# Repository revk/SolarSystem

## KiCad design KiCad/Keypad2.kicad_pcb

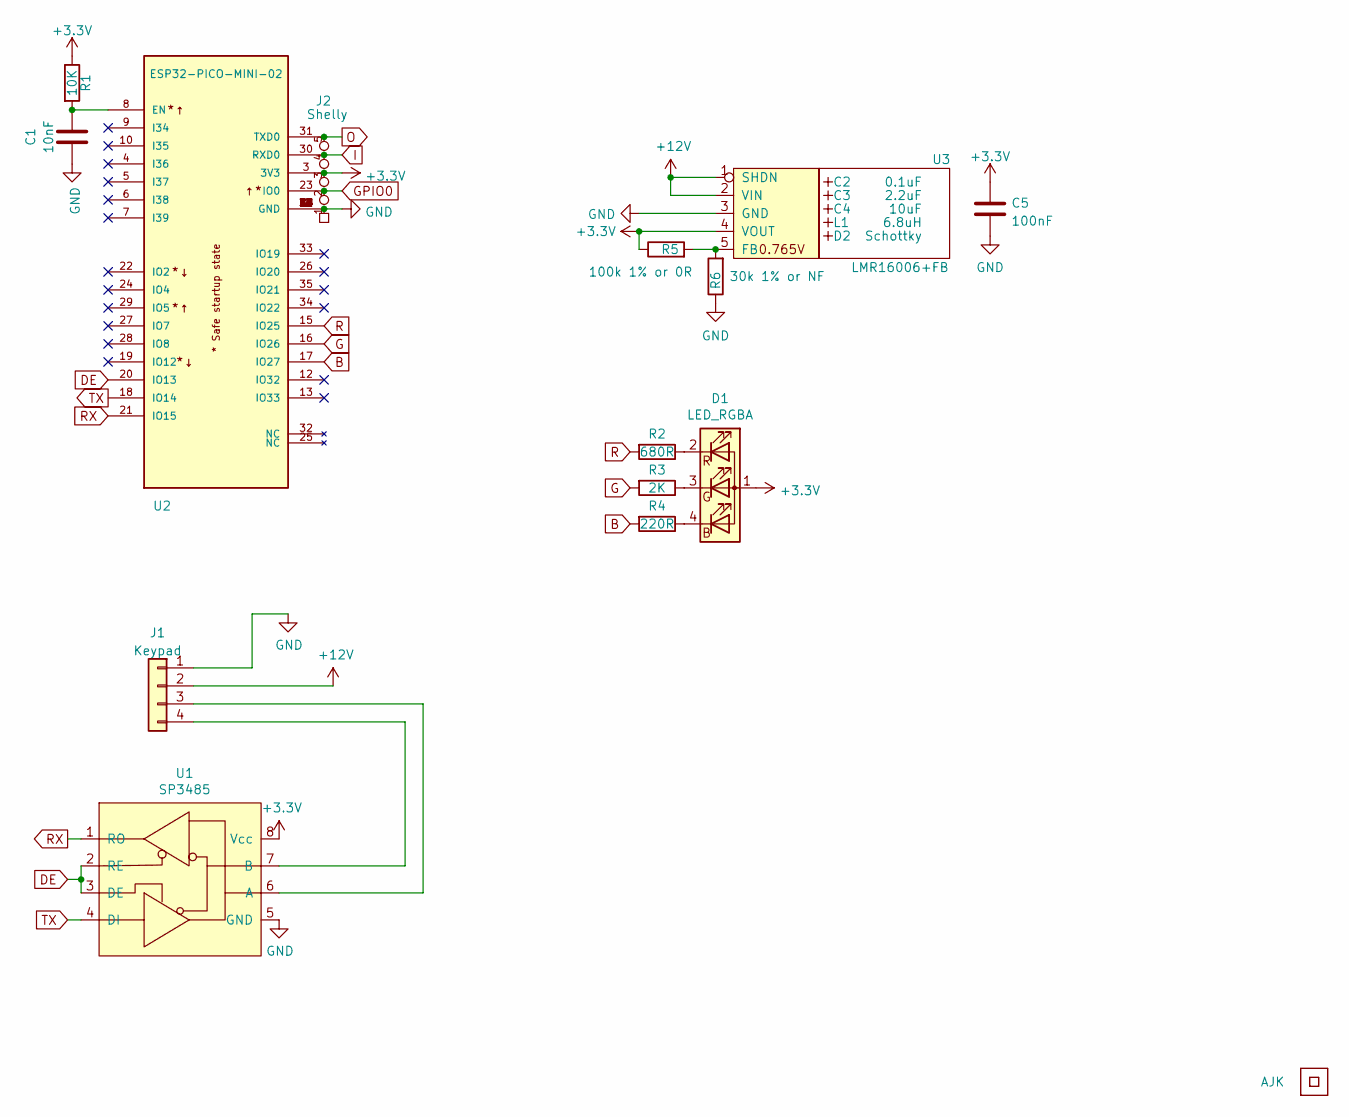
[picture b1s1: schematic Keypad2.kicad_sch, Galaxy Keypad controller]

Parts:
C1: 10nF; C_0603
C2: 0.1uF; C_0603_
C3: 2.2uF; C_0805_
C4: 10uF; C_0805_
C5: 100nF; C_0603
D1: LED_RGBA; LED-RGB-1.6x1.6
D2: Schottky; D_1206_; Part No CD1206-B2100
J1: Keypad; Molex_MiniSPOX_H4V
J2: Shelly
L1: 6.8uH; L_4x4_; Part No TYA4020
Logo1: AJK
R1: 10K; R_0603
R2: 680R; R_0603
R3: 2K; R_0603
R4: 220R; R_0603
R5: 100k 1% or 0R; R_0603
R6: 30k 1% or NF; R_0603
U1: SP3485; SO-8_3.9x4.9mm_P1.27mm
U2: ESP32-PICO-MINI-02; PARTREV v1.0
U3: LMR16006+FB; SOT-23-Thin-6-Reg; Part No LMR16006YQ3
U4: QR; QR-SS

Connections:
+3V3: C5.1, D1.1 (A), J2.3 (3V3), R1.1, R5.1, U1.8 (Vcc), U2.3 (3V3), U3.4 (VOUT)
+12V: J1.2, U3.1 (SHDN), U3.2 (VIN)
B: R4.2, U2.17 (IO27)
DE: U1.2 (RE), U1.3 (DE), U2.20 (IO13)
G: R3.2, U2.16 (IO26)
GND: C1.1, C5.2, J1.1, J2.1 (GND), R6.1, U1.5 (GND), U2.1 (GND), U2.2 (GND), U2.11 (GND), U2.14 (GND), U2.36 (GND), U2.37 (GND), U2.38 (GND), U2.39 (GND), U2.40 (GND), U2.41 (GND), U2.42 (GND), U2.43 (GND), U2.44 (GND), U2.45 (GND), U2.46 (GND), U2.47 (GND), U2.48 (GND), U2.49 (GND), U2.50 (GND), U2.51 (GND), U2.52 (GND), U2.53 (GND), U3.3 (GND)
GPIO0: J2.2 (0), U2.23 (IO0)
I: J2.4 (Rx), U2.30 (RXD0)
unnamed: C1.2, R1.2, U2.8 (EN)
unnamed: D1.2 (RK), R2.1
unnamed: D1.3 (GK), R3.1
unnamed: D1.4 (BK), R4.1
unnamed: J1.3, U1.6 (A)
unnamed: J1.4, U1.7 (B)
unnamed: R5.2, R6.2, U3.5 (FB)
O: J2.5 (Tx), U2.31 (TXD0)
R: R2.2, U2.15 (IO25)
RX: U1.1 (RO), U2.21 (IO15)
TX: U1.4 (DI), U2.18 (IO14)

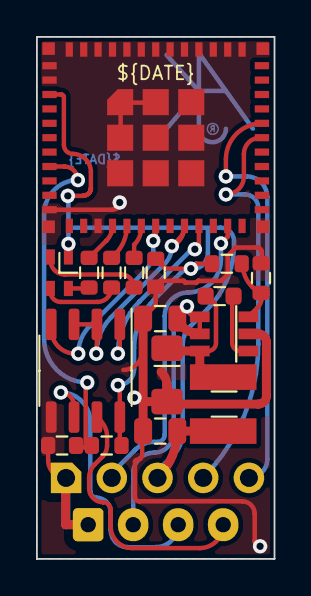
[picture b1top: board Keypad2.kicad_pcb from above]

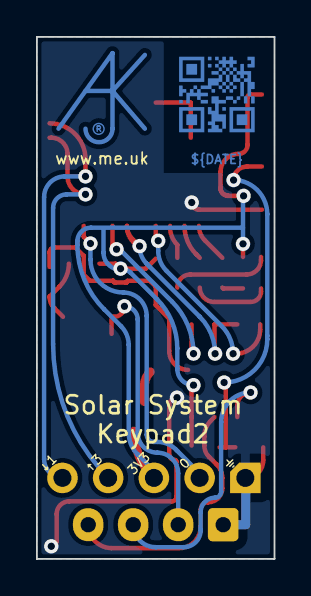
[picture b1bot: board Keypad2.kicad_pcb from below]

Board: 2 copper layers, 13.2 x 29.0 mm, 21 parts (3 on the bottom side), 19 nets.

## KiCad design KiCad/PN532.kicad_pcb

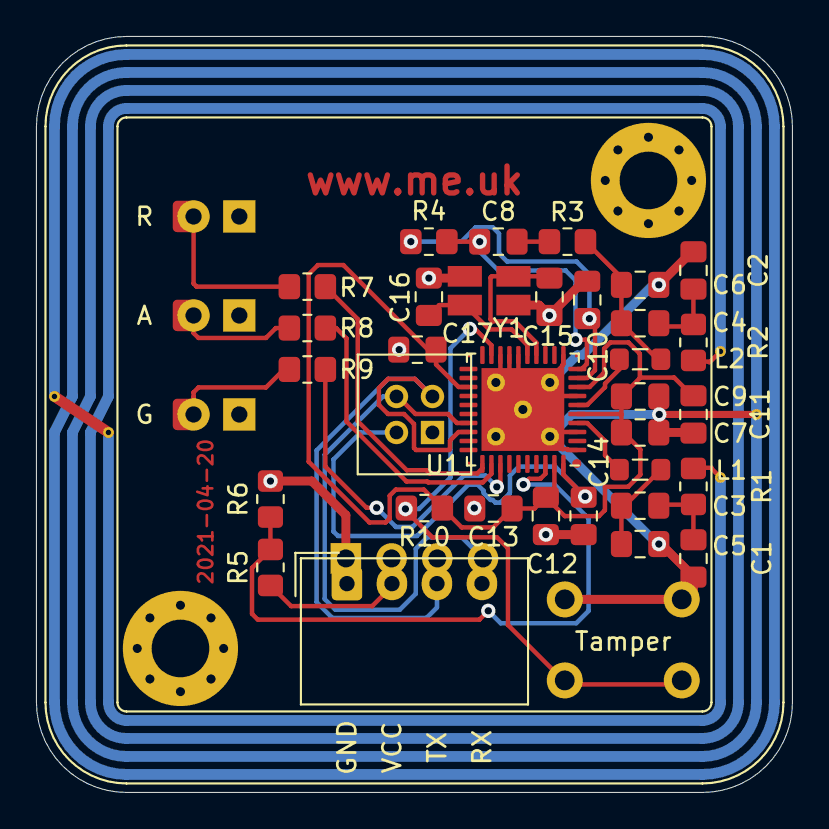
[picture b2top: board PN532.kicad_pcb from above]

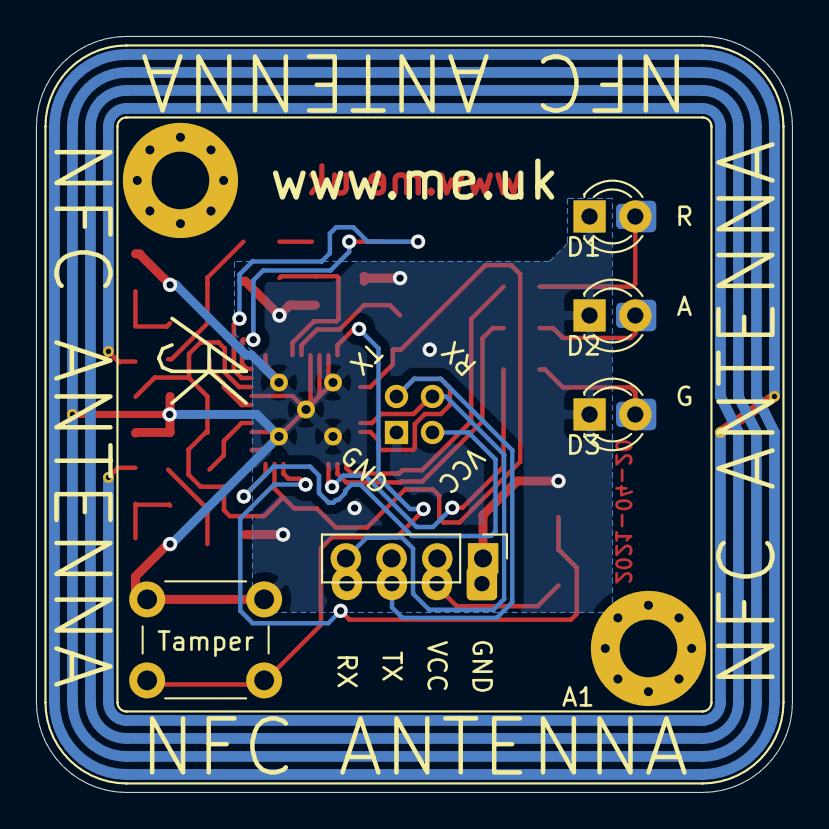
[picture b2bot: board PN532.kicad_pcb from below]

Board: 2 copper layers, 42.0 x 42.0 mm, 42 parts (7 on the bottom side), 26 nets.

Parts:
A1: PN532-Antenna
AJK1: AJK; AJK-Silk
C1, C2: 200pF; C_0805_2012Metric_Pad1.18x1.45mm_HandSolder
C3, C4, C15, C16: 22pF; C_0805_2012Metric_Pad1.18x1.45mm_HandSolder
C5, C6: 220pF; C_0805_2012Metric_Pad1.18x1.45mm_HandSolder
C7, C10, C11, C12, C14, C17: 0.1uF; C_0805_2012Metric_Pad1.18x1.45mm_HandSolder
C8: 1nF; C_0805_2012Metric_Pad1.18x1.45mm_HandSolder
C9, C13: 4.7uF; C_0805_2012Metric_Pad1.18x1.45mm_HandSolder
D1: RED; LED_D3.0mm_and_SMD
D2: AMBER; LED_D3.0mm_and_SMD
D3: GREEN; LED_D3.0mm_and_SMD
H1, H2: MountingHole; MountingHole_3.2mm_M3_Pad_Via
J1: Header; PinHeader_1x04_P2.54mm_Vertical
J2: SPOX; Molex_SPOX_5268-04A_1x04_P2.50mm_Horizontal
J3: MiniGrid; Connector-MilliGrid-2x2
L1, L2: 560nH; L_0805_2012Metric_Pad1.05x1.20mm_HandSolder
R1, R2: 2R; R_0805_2012Metric_Pad1.20x1.40mm_HandSolder
R3: 2K7; R_0805_2012Metric_Pad1.20x1.40mm_HandSolder
R4: 1K; R_0805_2012Metric_Pad1.20x1.40mm_HandSolder
R5, R10: 10K; R_0805_2012Metric_Pad1.20x1.40mm_HandSolder
R6: 20K; R_0805_2012Metric_Pad1.20x1.40mm_HandSolder
R7, R8, R9: 680R; R_0805_2012Metric_Pad1.20x1.40mm_HandSolder
SW1: TAMPER; SW_PUSH_6mm
U1: PN532; QFN-40-(hand)-1EP_6x6mm_P0.5mm_EP4.6x4.6mm
Y1: 27.12MHz (Mouser 830053099); Crystal-3.4x2.7

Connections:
+3V3: C7.1, C9.1, C11.1, C12.1, C13.1, C17.1, R10.1, U1.5, U1.8, U1.23, U1.39
+5V: C14.1, J1.2, J2.2, J3.2, R5.2, U1.40
GND: A1.2, C1.2, C2.1, C5.1, C6.1, C7.2, C9.2, C10.2, C11.2, C12.2, C13.2, C14.2, C15.2, C16.2, C17.2, D1.1, D2.1, D3.1, J1.1, J2.1, J3.1, R6.1, SW1.1, U1.1, U1.3, U1.7, U1.11, U1.16, U1.17, U1.18, U1.41, Y1.2, Y1.4
unnamed: A1.1, R1.2
unnamed: A1.3, R2.2
unnamed: C1.1, C3.2, R1.1
unnamed: C2.2, C4.1, R2.1
unnamed: C3.1, C5.2, L1.2
unnamed: C4.2, C6.2, L2.1, R3.2
unnamed: C8.1, R4.1, U1.10
unnamed: C8.2, R3.1
unnamed: C10.1, R4.2, U1.9
unnamed: C15.1, U1.14, Y1.1
unnamed: C16.1, U1.15, Y1.3
unnamed: D1.2, R7.2
unnamed: D2.2, R8.2
unnamed: D3.2, R9.2
unnamed: J1.3, J2.3, J3.3, U1.28
unnamed: J1.4, J2.4, J3.4, U1.27
unnamed: L1.1, U1.4
unnamed: L2.2, U1.6
unnamed: R5.1, R6.2, U1.38
unnamed: R7.1, U1.31
unnamed: R8.1, U1.32
unnamed: R9.1, U1.33
unnamed: R10.2, SW1.2, U1.19

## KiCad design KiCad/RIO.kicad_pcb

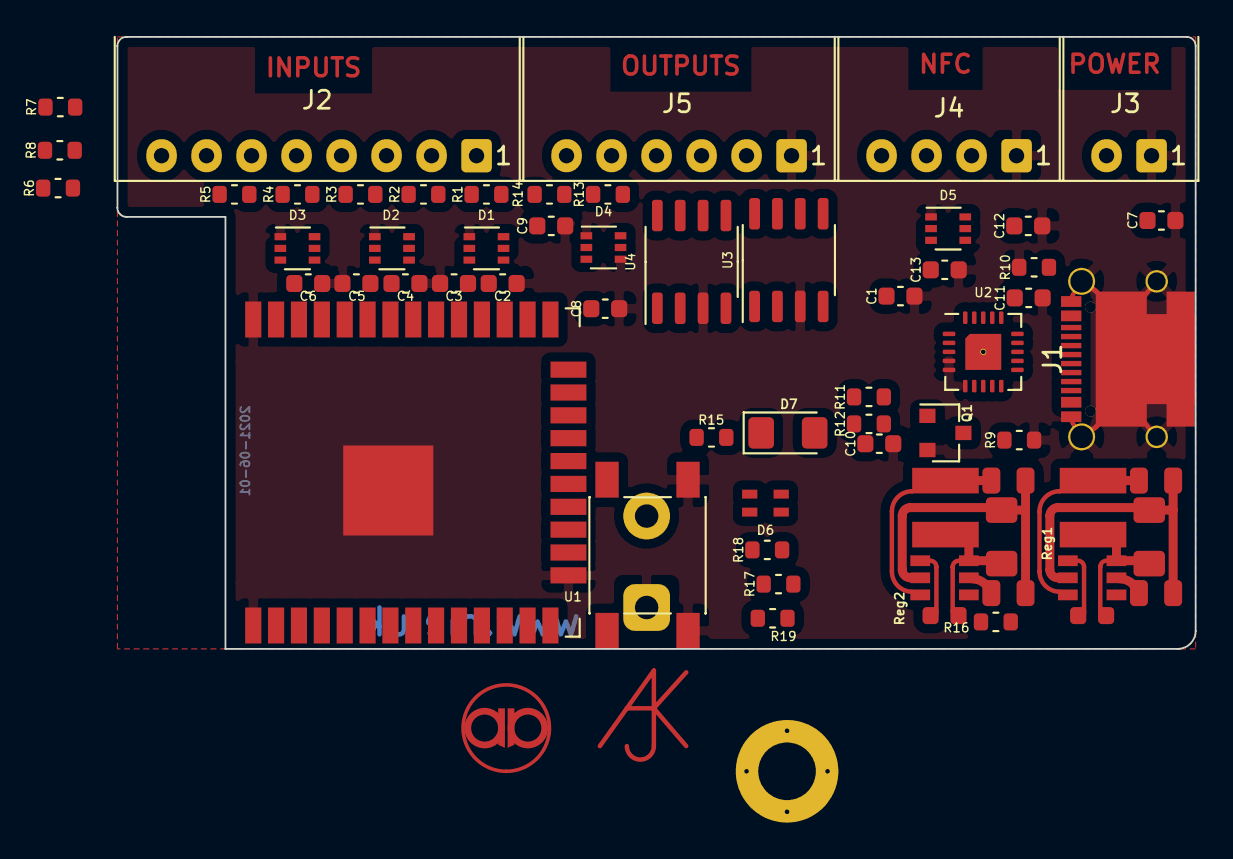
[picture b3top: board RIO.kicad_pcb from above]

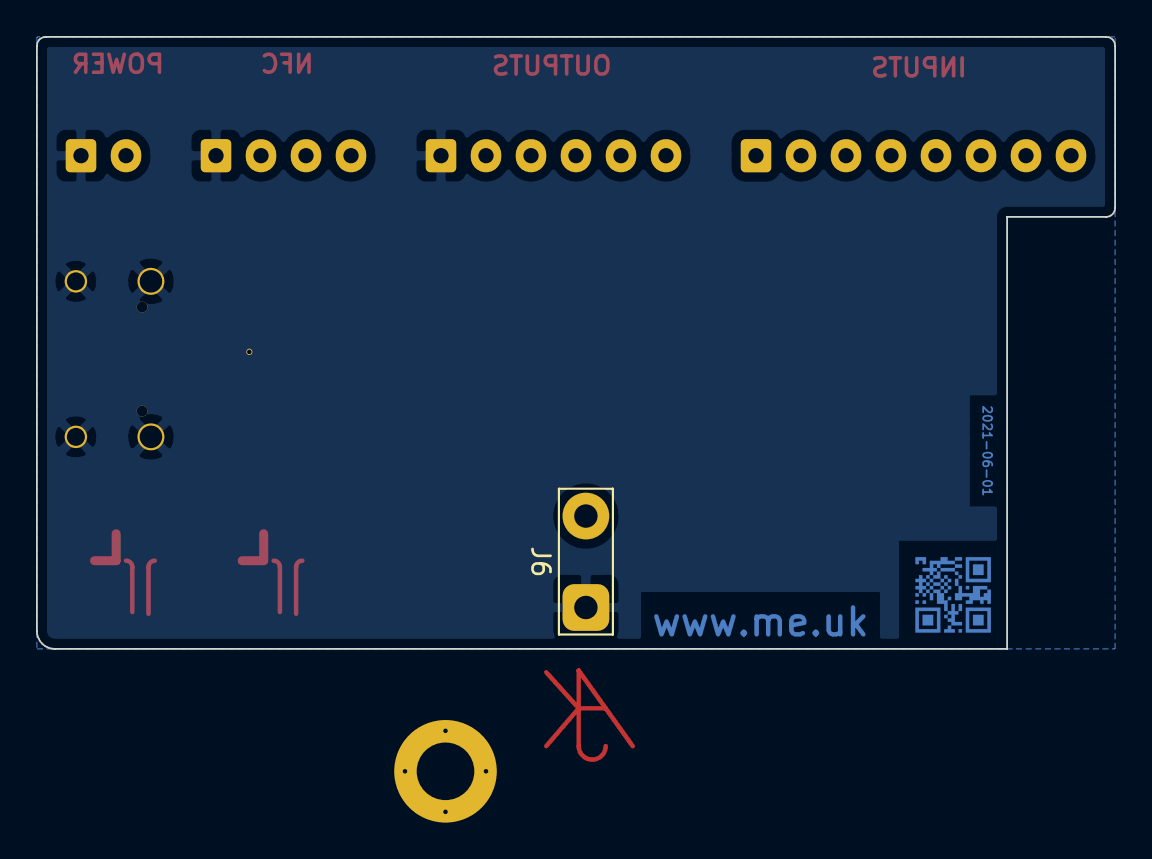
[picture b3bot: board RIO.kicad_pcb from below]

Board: 2 copper layers, 59.9 x 34.0 mm, 57 parts (2 on the bottom side), 55 nets, no tracks yet.

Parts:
AJK1: AJK
C1: 0.1uF; C_0603
C2, C3, C4, C5, C6, C7, C8, C9, C13: 33pF; C_0603
C10, C11: 47pF; C_0603
C12: 10nF; C_0603
D1, D2, D3, D4, D5: BAV99S; SOT-363_SC-70-6
D6: LED_RGBA; LED-RGB-1.6x1.6
D7: D; D_1206_3216Metric_Pad1.42x1.75mm_HandSolder
H1: MountingHole; ISO7380-M3-Pad
J1: USB-C; USC16-TR-Round
J2: INPUTS; Molex_MiniSPOX_H8RA
J3: POWER; Molex_MiniSPOX_H2RA
J4: RFID; Molex_MiniSPOX_H4RA
J5: OUTPUTS; Molex_MiniSPOX_H6RA
J6: ExtTamper; TestPoint_2Pads_Pitch5.08mm_Drill1.3mm
Q1: BC817; SOT-23
R1, R2, R3, R4, R5, R6, R7, R8, R13, R14: 100R; R_0603
R9, R10: 5K1; R_0603
R11, R12: 27R; R_0603
R15: 1k; R_0603
R16: 100K; R_0603
R17: 732R; R_0603
R18: 2K; R_0603
R19: 324R; R_0603
Reg1: 3.3V; RegulatorBlock
Reg2: 3.3V/5V; RegulatorBlock
SW1: Tamper; SW_PUSH_6mm_SMD
U1: ESP32-WROOM-32
U2: FT231XQ; QFN-20-1EP_4x4mm_P0.5mm_EP2.5x2.5mm
U3, U4: ISL89410; SO-8_3.9x4.9mm_P1.27mm
U5: AA
U6: QR; QR-SS

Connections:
+3V3: C1.1, D1.2, D1.5, D2.2, D2.5, D3.2, D3.5, D4.2, D4.5, D5.2, D5.5, D6.1, Reg1.4, U1.2, U2.10, U2.11, U2.12, U2.20
+5V: J4.2, Reg2.4
+12V: D7.1, J3.2, R16.2, Reg1.1, Reg1.2, Reg2.2
B: R19.2, U1.6
BOOT: U1.25, U2.18
D+: R12.1, U2.8
D-: R11.1, U2.9
EN: U1.3, U2.19
G: R18.2, U1.9
GND: C1.2, C2.2, C3.2, C4.2, C5.2, C6.2, C7.2, C8.2, C9.2, C10.2, C11.2, C12.2, C13.2, D1.1, D1.4, D2.1, D2.4, D3.1, D3.4, D4.1, D4.4, D5.1, D5.4, H1.1, J1.A1, J1.A12, J1.B1, J1.B12, J1.S1, J3.1, J4.1, J5.1, J6.1, Q1.2, R9.2, R10.1, Reg1.3, Reg2.3, SW1.1, U1.1, U1.15, U1.38, U1.39, U2.2, U2.3, U2.4, U2.5, U2.6, U2.13, U2.21, U3.3, U4.3
I: U1.34, U2.17
IN1: C2.1, D1.6, R1.2, U1.29
IN2: C3.1, D1.3, R2.2, U1.30
IN3: C4.1, D2.6, R3.2, U1.31
IN4: C5.1, D2.3, R4.2, U1.33
IN5: C6.1, D3.6, R5.2, U1.36
IN6: C7.1, D3.3, R6.2, U1.37
IN7: C8.1, D4.6, R7.2, U1.10
IN8: C9.1, D4.3, R8.2, U1.11
unnamed: C10.1, J1.A6, J1.B6, R12.2
unnamed: C11.1, J1.A7, J1.B7, R11.2
unnamed: D6.2, R17.1
unnamed: D6.3, R18.1
unnamed: D6.4, R19.1
unnamed: J1.A5, R9.1
unnamed: J1.B5, R10.2
unnamed: J2.1, R1.1
unnamed: J2.2, R2.1
unnamed: J2.3, R3.1
unnamed: J2.4, R4.1
unnamed: J2.5, R5.1
unnamed: J2.6, R6.1
unnamed: J2.7, R7.1
unnamed: J2.8, R8.1
unnamed: J4.3, R13.1
unnamed: J4.4, R14.1
unnamed: J5.2, U3.6, U4.6
unnamed: J5.3, U3.7
unnamed: J5.4, U3.5
unnamed: J5.5, U4.7
unnamed: J5.6, U4.5
unnamed: Q1.1, R15.1
unnamed: Q1.3, R16.1, Reg2.1
O: U1.35, U2.1
OUT1: U1.23, U3.2
OUT2: U1.14, U3.4
OUT3: U1.24, U4.2
OUT4: U1.12, U4.4
R: R17.2, U1.13
RFRX: C13.1, D5.6, R13.2, U1.27
RFTX: D5.3, R14.2, U1.28
SHDN: R15.2, U1.26
TAMPER: J6.2, SW1.2, U1.16
USB: U1.8, U2.15
VBUS: C12.1, D7.2, J1.A4, J1.A9, J1.B4, J1.B9

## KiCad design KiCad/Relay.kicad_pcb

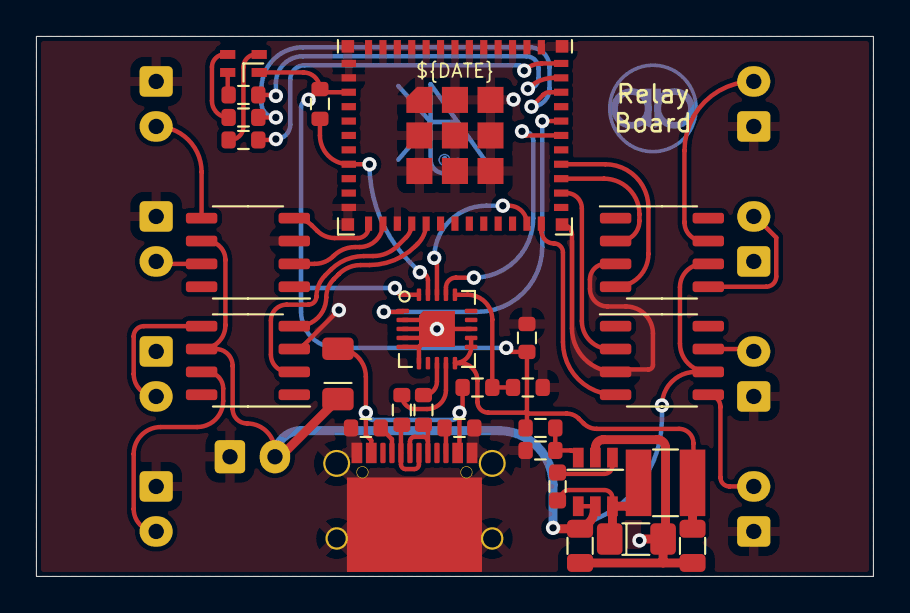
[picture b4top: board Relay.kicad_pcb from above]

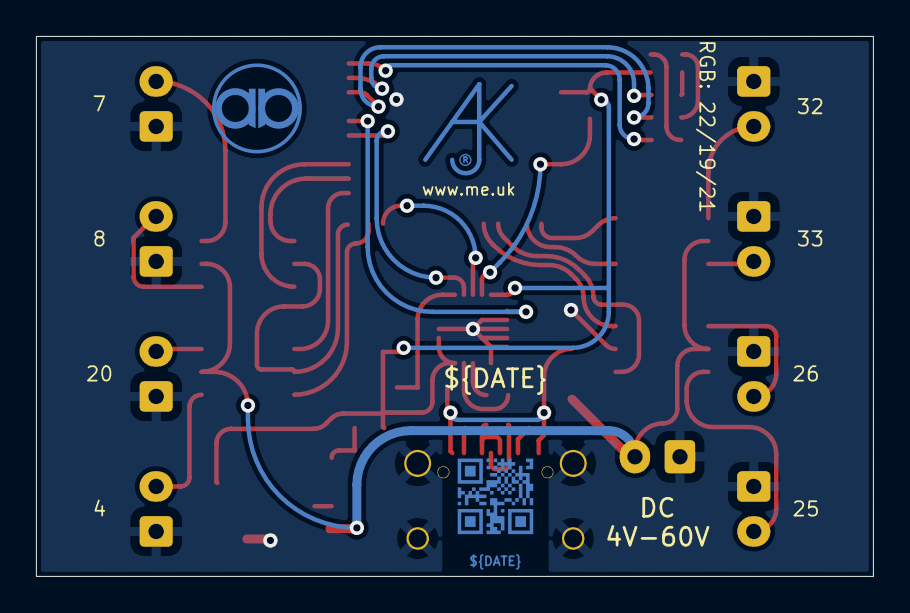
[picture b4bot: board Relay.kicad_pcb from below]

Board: 2 copper layers, 46.5 x 30.0 mm, 40 parts (3 on the bottom side), 38 nets.

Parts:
AJK1: AJK
C1: 0.1uF; C_0603
C2: 0.1uF; Hidden
C3: 2.2uF; Hidden
C4: 10uF; Hidden
D1: LED_RGBA; LED-RGB-1.6x1.6
D2: D; D_1206
D3: Schottky; Hidden
J1: USB-C; USC16-TR-Round
J2: POWER; Molex_MiniSPOX_H2RA
J3: O1; Molex_MiniSPOX_H2RA
J4: O2; Molex_MiniSPOX_H2RA
J5: O3; Molex_MiniSPOX_H2RA
J6: O4; Molex_MiniSPOX_H2RA
J7: O5; Molex_MiniSPOX_H2RA
J8: O6; Molex_MiniSPOX_H2RA
J9: O7; Molex_MiniSPOX_H2RA
J10: O8; Molex_MiniSPOX_H2RA
L1: 6.8uH; Hidden
R1, R3: 10k; R_0603
R2: 4k7; R_0603
R4, R5: 5K1; R_0603
R6, R7: 27R; R_0603
R8: 680R; R_0603
R9: 2K; R_0603
R10: 220R; R_0603
R11: 100k 1% or 0R; R_0603
R12: 30k 1% or NF; R_0603
U1: ESP32-PICO-MINI-02
U2: FT231XQ; QFN-20-1EP_4x4mm_P0.5mm_EP2.5x2.5mm
U3, U4, U5, U6: ISL89410; SO-8_3.9x4.9mm_P1.27mm
U7: LMR16006+FB; RegulatorBlockFB
U8: AA
U9: QR; QR-SS

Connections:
+3V3: C1.1, D1.1 (A), R1.2, R11.1, U1.3 (3V3), U2.10 (3V3OUT), U2.11 (~RESET), U2.12 (VCC), U2.20 (VCCIO), U7.4 (VOUT)
+12V: D2.1 (K), J2.2 (DC), U3.6 (V+), U4.6 (V+), U5.6 (V+), U6.6 (V+), U7.1 (SHDN), U7.2 (VIN)
B: R10.2, U1.35 (IO21)
BOOT: U1.23 (IO0), U2.18 (~DTR)
D+: R7.1, U2.8 (USBDP)
D-: R6.2, U2.9 (USBDM)
EN: R1.1, U1.8 (EN), U2.19 (~RTS)
G: R9.2, U1.33 (IO19)
GND: C1.2, J1.A1 (GND), J1.A12 (GND), J1.B1 (GND), J1.B12 (GND), J1.S1 (SHIELD), J2.1 (GND), J3.1, J4.1, J5.1, J6.1, J7.1, J8.1, J9.1, J10.1, R3.2, R4.2, R5.1, R12.1, U1.1 (GND), U1.2 (GND), U1.11 (GND), U1.14 (GND), U1.36 (GND), U1.37 (GND), U1.38 (GND), U1.39 (GND), U1.40 (GND), U1.41 (GND), U1.42 (GND), U1.43 (GND), U1.44 (GND), U1.45 (GND), U1.46 (GND), U1.47 (GND), U1.48 (GND), U1.49 (GND), U1.50 (GND), U1.51 (GND), U1.52 (GND), U1.53 (GND), U2.2 (~RI), U2.3 (GND), U2.4 (~DSR), U2.5 (~DCD), U2.6 (~CTS), U2.13 (GND), U2.21 (GND), U3.3 (GND), U4.3 (GND), U5.3 (GND), U6.3 (GND), U7.3 (GND)
I: U1.30 (RXD0), U2.17 (TXD)
unnamed: D1.2 (RK), R8.1
unnamed: D1.3 (GK), R9.1
unnamed: D1.4 (BK), R10.1
unnamed: J1.A5 (CC1), R4.1
unnamed: J1.A6 (D+), J1.B6 (D+), R7.2
unnamed: J1.A7 (D-), J1.B7 (D-), R6.1
unnamed: J1.B5 (CC2), R5.2
unnamed: R2.2, R3.1, U2.16 (CBUS3)
unnamed: R11.2, R12.2, U7.5 (FB)
O: U1.31 (TXD0), U2.1 (RXD)
O1: J3.2, U3.5 (OUT_B)
O2: J4.2, U3.7 (OUT_A)
O3: J5.2, U5.5 (OUT_B)
O4: J6.2, U5.7 (OUT_A)
O5: J7.2, U4.5 (OUT_B)
O6: J8.2, U4.7 (OUT_A)
O7: J9.2, U6.5 (OUT_B)
O8: J10.2, U6.7 (OUT_A)
OUT1: U1.12 (IO32), U3.4 (IN_B)
OUT2: U1.13 (IO33), U3.2 (IN_A)
OUT3: U1.16 (IO26), U5.4 (IN_B)
OUT4: U1.15 (IO25), U5.2 (IN_A)
OUT5: U1.24 (IO4), U4.4 (IN_B)
OUT6: U1.26 (IO20), U4.2 (IN_A)
OUT7: U1.28 (IO8), U6.4 (IN_B)
OUT8: U1.27 (IO7), U6.2 (IN_A)
R: R8.2, U1.34 (IO22)
VBUS: D2.2 (A), J1.A4 (VBUS), J1.A9 (VBUS), J1.B4 (VBUS), J1.B9 (VBUS), R2.1

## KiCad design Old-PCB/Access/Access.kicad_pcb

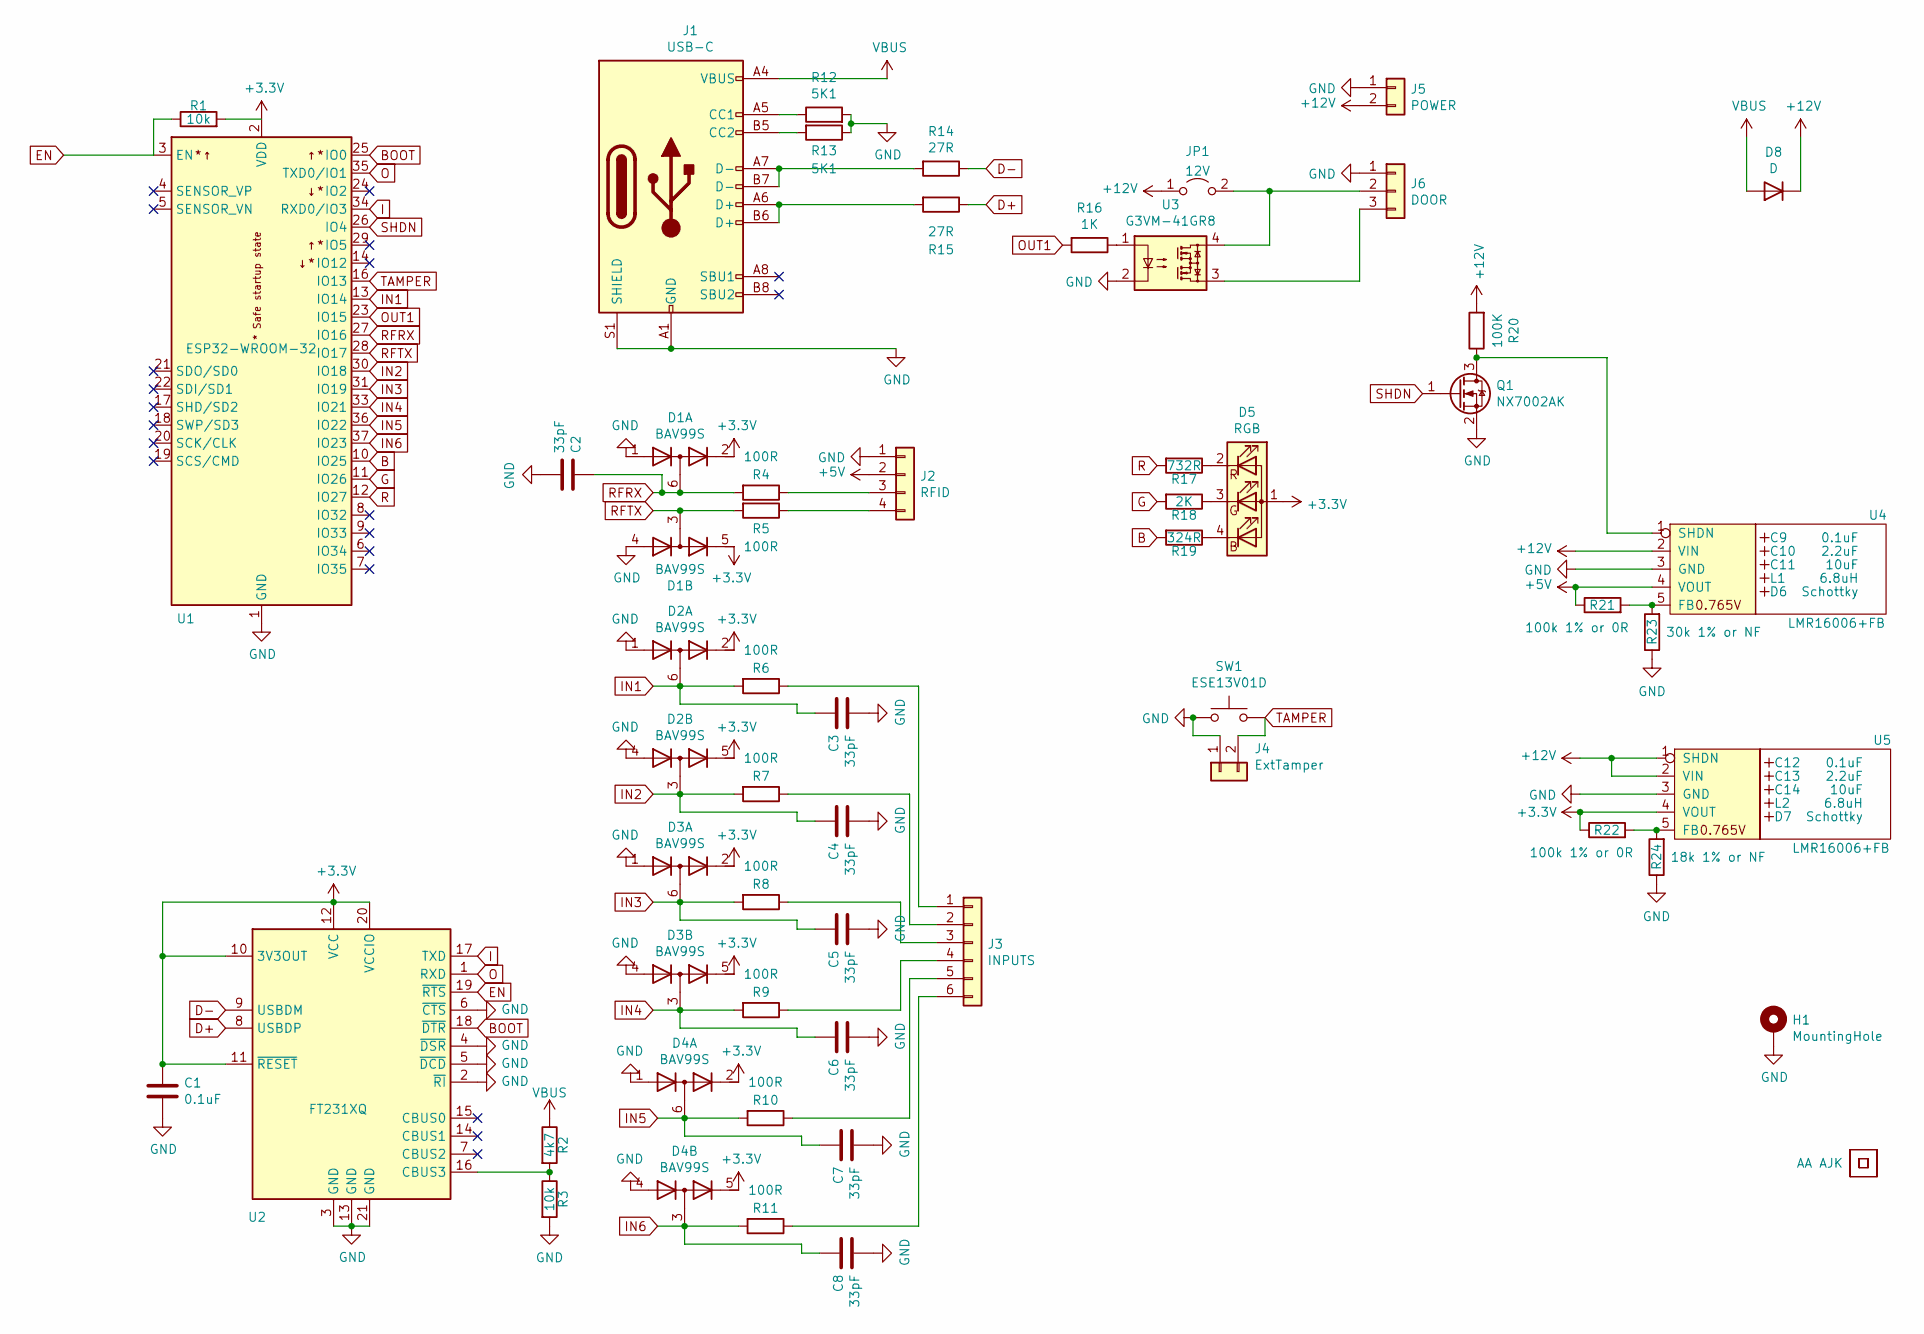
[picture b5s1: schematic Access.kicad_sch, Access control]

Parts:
AJK1: AJK
C1: 0.1uF; C_0603
C2, C3, C4, C5, C6, C7, C8: 33pF; C_0603
C9, C12: 0.1uF; Hidden
C10, C13: 2.2uF; Hidden
C11, C14: 10uF; Hidden
D1, D2, D3, D4: BAV99S; SOT-363_SC-70-6
D5: RGB; LED-RGB-1.6x1.6; Part No APTF1616LSEEZGKQBKC
D6, D7: Schottky; Hidden; Part No CD1206-B2100
D8: D; D_1206_3216Metric_Pad1.42x1.75mm_HandSolder
H1: MountingHole; ISO7380-M3-Pad
J1: USB-C; USC16-TR-Round
J2: RFID; Molex_MiniSPOX_H4RA
J3: INPUTS; Molex_MiniSPOX_H6RA
J4: ExtTamper; PinHeader_1x02_P2.54mm_Vertical
J5: POWER; Molex_MiniSPOX_H2RA
J6: DOOR; Molex_MiniSPOX_H3RA
JP1: 12V; PinHeader_1x02_P1.27mm_Vertical
L1, L2: 6.8uH; Hidden; Part No TYA4020
Q1: NX7002AK; SOT-23; Part No NX7002AK
R1, R3: 10k; R_0603
R2: 4k7; R_0603
R4, R5, R6, R7, R8, R9, R10, R11: 100R; R_0603
R12, R13: 5K1; R_0603
R14, R15: 27R; R_0603
R16: 1K; R_0603_1608Metric_Pad0.98x0.95mm_HandSolder
R17: 732R; R_0603
R18: 2K; R_0603
R19: 324R; R_0603
R20: 100K; R_0603
R21, R22: 100k 1% or 0R; R_0603
R23: 30k 1% or NF; R_0603
R24: 18k 1% or NF; R_0603
SW1: ESE13V01D; ESE13
U1: ESP32-WROOM-32
U2: FT231XQ; QFN-20-1EP_4x4mm_P0.5mm_EP2.5x2.5mm
U3: G3VM-41GR8; Special-SOP-4-3.7x4.55
U4, U5: LMR16006+FB; RegulatorBlockFB; Part No LMR16006YQ3
U6: AA
U7: QR; QR-SS

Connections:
+3V3: C1.1, D1.2 (K2), D1.5 (K4), D2.2 (K2), D2.5 (K4), D3.2 (K2), D3.5 (K4), D4.2 (K2), D4.5 (K4), D5.1 (A), R1.2, R22.1, U1.2 (VDD), U2.10 (3V3OUT), U2.11 (~RESET), U2.12 (VCC), U2.20 (VCCIO), U5.4 (VOUT)
+5V: J2.2, R21.1, U4.4 (VOUT)
+12V: D8.1 (K), J5.2, JP1.1 (A), R20.2, U4.2 (VIN), U5.1 (SHDN), U5.2 (VIN)
B: R19.2, U1.10 (IO25)
BOOT: U1.25 (IO0), U2.18 (~DTR)
D+: R15.1, U2.8 (USBDP)
D-: R14.1, U2.9 (USBDM)
EN: R1.1, U1.3 (EN), U2.19 (~RTS)
G: R18.2, U1.11 (IO26)
GND: C1.2, C2.2, C3.2, C4.2, C5.2, C6.2, C7.2, C8.2, D1.1 (A1), D1.4 (A3), D2.1 (A1), D2.4 (A3), D3.1 (A1), D3.4 (A3), D4.1 (A1), D4.4 (A3), H1.1, J1.A1 (GND), J1.A12 (GND), J1.B1 (GND), J1.B12 (GND), J1.S1 (SHIELD), J2.1, J4.1, J5.1, J6.1, Q1.2 (S), R3.2, R12.2, R13.1, R23.1, R24.1, SW1.1, U1.1 (GND), U1.15 (GND), U1.38 (GND), U1.39 (GND), U2.2 (~RI), U2.3 (GND), U2.4 (~DSR), U2.5 (~DCD), U2.6 (~CTS), U2.13 (GND), U2.21 (GND), U3.2, U4.3 (GND), U5.3 (GND)
I: U1.34 (RXD0/IO3), U2.17 (TXD)
IN1: C3.1, D2.6 (K3A4), R6.2, U1.13 (IO14)
IN2: C4.1, D2.3 (K1A2), R7.2, U1.30 (IO18)
IN3: C5.1, D3.6 (K3A4), R8.2, U1.31 (IO19)
IN4: C6.1, D3.3 (K1A2), R9.2, U1.33 (IO21)
IN5: C7.1, D4.6 (K3A4), R10.2, U1.36 (IO22)
IN6: C8.1, D4.3 (K1A2), R11.2, U1.37 (IO23)
unnamed: D5.2 (RK), R17.1
unnamed: D5.3 (GK), R18.1
unnamed: D5.4 (BK), R19.1
unnamed: J1.A5 (CC1), R12.1
unnamed: J1.A6 (D+), J1.B6 (D+), R15.2
unnamed: J1.A7 (D-), J1.B7 (D-), R14.2
unnamed: J1.B5 (CC2), R13.2
unnamed: J2.3, R4.1
unnamed: J2.4, R5.1
unnamed: J3.1, R6.1
unnamed: J3.2, R7.1
unnamed: J3.3, R8.1
unnamed: J3.4, R9.1
unnamed: J3.5, R10.1
unnamed: J3.6, R11.1
unnamed: J6.2, JP1.2 (B), U3.4
unnamed: J6.3, U3.3
unnamed: Q1.3 (D), R20.1, U4.1 (SHDN)
unnamed: R2.2, R3.1, U2.16 (CBUS3)
unnamed: R16.1, U3.1
unnamed: R21.2, R23.2, U4.5 (FB)
unnamed: R22.2, R24.2, U5.5 (FB)
O: U1.35 (TXD0/IO1), U2.1 (RXD)
OUT1: R16.2, U1.23 (IO15)
R: R17.2, U1.12 (IO27)
RFRX: C2.1, D1.6 (K3A4), R4.2, U1.27 (IO16)
RFTX: D1.3 (K1A2), R5.2, U1.28 (IO17)
SHDN: Q1.1 (G), U1.26 (IO4)
TAMPER: J4.2, SW1.2, U1.16 (IO13)
VBUS: D8.2 (A), J1.A4 (VBUS), J1.A9 (VBUS), J1.B4 (VBUS), J1.B9 (VBUS), R2.1

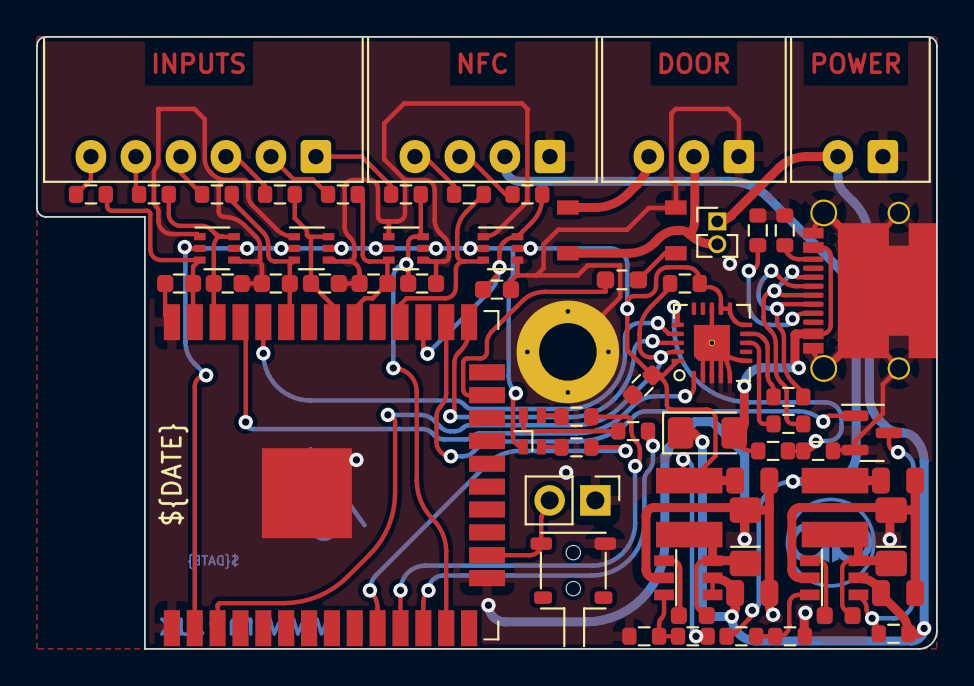
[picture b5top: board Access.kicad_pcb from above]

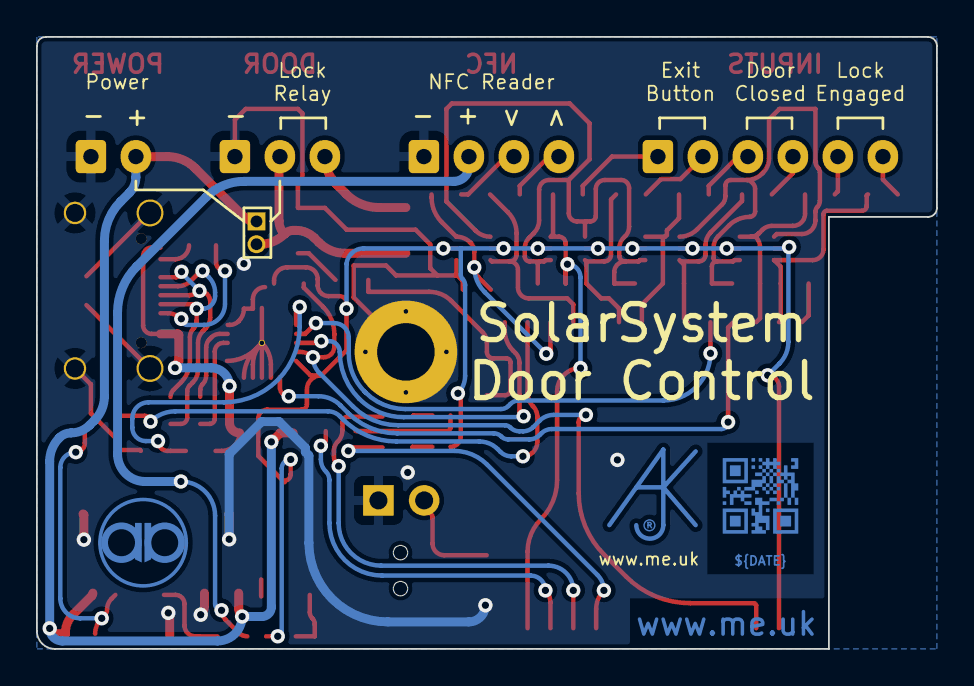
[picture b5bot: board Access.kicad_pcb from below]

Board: 2 copper layers, 50.0 x 34.0 mm, 66 parts (3 on the bottom side), 47 nets.
